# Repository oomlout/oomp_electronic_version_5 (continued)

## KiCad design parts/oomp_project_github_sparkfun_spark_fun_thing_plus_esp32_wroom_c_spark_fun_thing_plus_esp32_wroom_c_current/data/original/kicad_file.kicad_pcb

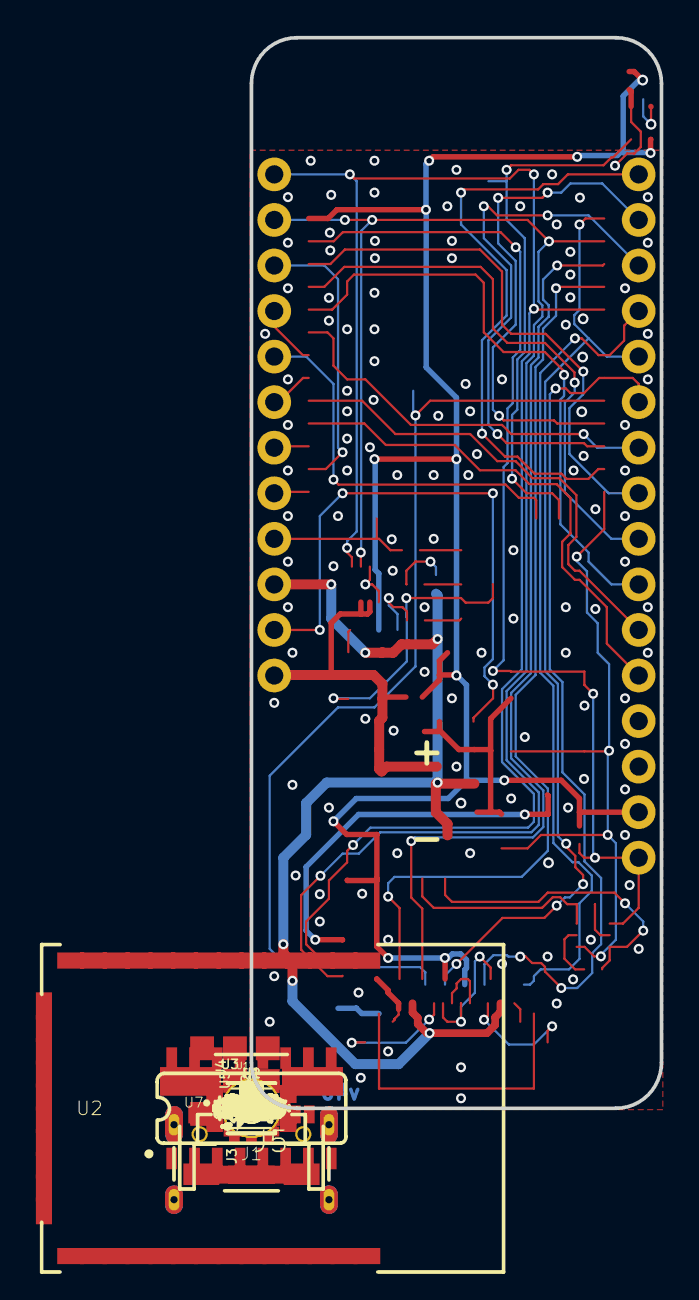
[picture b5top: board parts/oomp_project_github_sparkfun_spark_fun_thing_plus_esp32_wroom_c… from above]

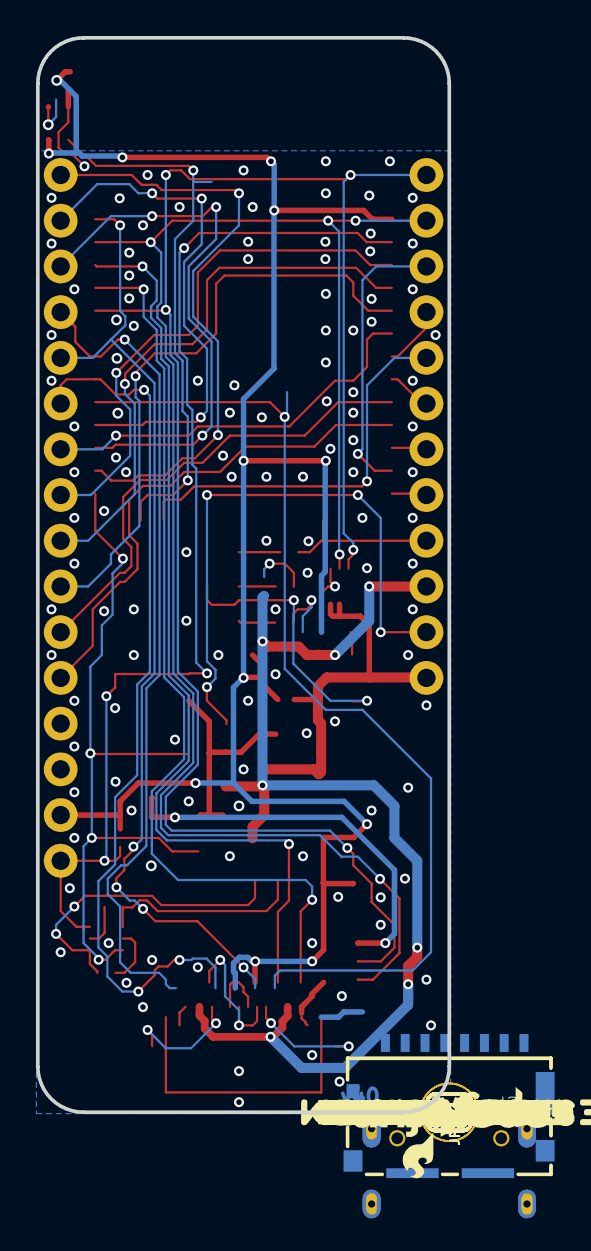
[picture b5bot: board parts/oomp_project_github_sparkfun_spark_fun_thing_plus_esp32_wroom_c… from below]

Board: 2 copper layers, 22.9 x 59.7 mm, 110 parts (46 on the bottom side), 51 nets.

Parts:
C1, C4: 10uF; 0402-TIGHT
C2, C5, C15: 0.1uF; 0402-TIGHT
C3, C7, C10: 1.0uF; 0402-TIGHT
C6: 4.7uF; 0402-TIGHT
C19: 4.7uF; 0603
D1: Yellow; LED-0603
D3: BLUE; LED-0603
D4: 3A/10V/280mV; SOD-323
D5: WS2812; WS2812-2020
D12: RED; LED-0603
FD1, FD2, FD3, FD4: FIDUCIALUFIDUCIAL; FIDUCIAL-MICRO
FRAME1: FRAME-LEDGER; CREATIVE_COMMONS
H1, H2: STAND-OFFTIGHT; STAND-OFF-TIGHT
J1: USB-C-16P-2LAYER-PADS
J2: MICRO-SDFRICTION; MICROSD_TINY
J3: QWIIC_RA; JST04_1MM_RA
J4: JST-2-SMD
J5: THING_PLUS_LOGICAL; THING_PLUS
JP1, JP2, JP3: JUMPER-SMT_2_NC_TRACE_SILK; SMT-JUMPER_2_NC_TRACE_SILK
LOGO1: SFE_LOGO_NAME_FLAME.1_INCH; SFE_LOGO_NAME_FLAME_.1
LOGO2: OSHW-LOGOMINI; OSHW-LOGO-MINI
LOGO4: QWIIC_LOGO_4MM; QWIIC_4MM
Q2: MBT3904DW1T1; SC70-6
Q3: 20V/4.2A/52mΩ/1.4W; SOT23-3
R2, R7, R8, R17, R18: 10k; 0402-TIGHT
R3, R4, R34: 1k; 0402-TIGHT
R6: 2.0k; 0603
R9, R10: 5.1k; 0402-TIGHT
S3: Boot; TACTILE_SWITCH_SMD_4.6X2.8MM
S4: Reset; TACTILE_SWITCH_SMD_4.6X2.8MM
TP1, TP2, TP3, TP4: TEST-POINT3X5; PAD.03X.05
U1: MCP73831; SOT23-5
U2: ESP-WROOM-3232D-NARROW; ESP-WROOM-32D-NARROW
U3, U5: 3.3V; SOT23-5
U4: MAX17048; DFN-8
U7: CH340C; SO016
U$1: SFE_LOGO_FLAME_STOP_.1
U$2: #23#PICO#0
U$3: #19#POCI#0
U$4: #4#FREE#0
U$5: #CHG_LED#0
U$6: ESP32#WROOM0
U$7: THING_PLUS_C0
U$8: #SHLD#0
U$9: #_GND#0
U$10: #_NC#0
U$11: #_3V3#0
U$12: SFE_LOGO_FLAME_.1
U$23: 3V30
U$24: CHG1
U$25: PWR2
U$26: STAT0
U$68: A03
U$69: A12
U$70: A21
U$71: A30
U$72: #17#TX#0
U$73: VB1
U$74: EN3
U$75: GND1
U$76: VU0
U$77: 130
U$78: BOOT0
U$79, U$109: #RST#0
U$80: RST0
U$81: #16#RX#0
U$83: #18#SCK#0
U$84: #35#A5#0
U$85: #36#A4#0
U$86: #25#A1#2
U$87: #26#A0#3
U$88: #34#A2#1
U$89: #39#A3#0
U$90: #12#4
U$91: #14#9
U$92: #15#7
U$93: #27#5
U$94: #32#8
U$95: #33#6
U$96: #EN#1
U$97: #VBAT#0
U$98: #VUSB#2
U$99: #13#LED#0
U$100: #21#SDA#1
U$101: #22#SCL#0
U$102: #PWR#0
U$107: NC0

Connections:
3.3V: C1.1, C2.1, C4.1, C5.1, C10.1, D5.VCC, J2.4, J5.27, JP1.2, R2.2, U2.2, U3.5, U7.4, U7.16
CH340-DTR: Q2.1, R17.1, U7.13
CH340-RTS: Q2.4, R18.1, U7.14
CH340-RX: U2.35, U7.3
CH340-TX: U2.34, U7.2
CHG_LED: D1.A, R3.2
D+: J1.A6, J1.B6, U7.5
D-: J1.A7, J1.B7, U7.6
DTR-10K: Q2.5, R17.2
ESP_0/QPWR: Q2.6, S3.3, S3.4, TP1.1, U2.25, U5.3
ESP_2/RGB_DI: D5.DI, TP3.1, U2.24
ESP_4/TP_FB: J5.13, U2.26
ESP_5/SD_CS: J2.2, TP4.1, U2.29
ESP_12/GPIO1: J5.8, U2.14
ESP_13/GPIO0/LED: J5.9, R4.1, U2.16
ESP_14/GPIO6: J5.3, U2.13
ESP_15/GPIO4: J5.5, U2.23
ESP_16/TP_RX: J5.15, U2.27
ESP_17/TP_TX: J5.14, U2.28
ESP_18/TP_SCK: J2.5, J5.18, U2.30
ESP_19/TP_POCI: J2.7, J5.16, U2.31
ESP_21/TP_SDA: J3.3, J5.1, U2.33, U4.8
ESP_22/TP_SCL: J3.4, J5.2, U2.36, U4.7
ESP_23/TP_PICO: J2.3, J5.17, U2.37
ESP_25/TP_A1: J5.23, U2.10
ESP_26/TP_A0: J5.24, U2.11
ESP_27/GPIO2: J5.7, U2.12
ESP_32/GPIO5: J5.4, U2.8
ESP_33/GPIO3: J5.6, U2.9
ESP_34/TP_A2: J5.22, U2.6
ESP_35/TP_A5: J5.19, U2.7
ESP_36/TP_A4: J5.20, U2.4
ESP_39/TP_A3: J5.21, U2.5
GND: C1.2, C2.2, C3.2, C4.2, C5.2, C6.2, C7.2, C10.2, C15.2, C19.2, D3.C, D5.GND, D12.C, J1.GND, J1.GND2, J2.6, J2.GND1, J2.GND2, J2.GND3, J2.GND4, J2.GND5, J2.GND6, J3.1, J4.1, J5.25, JP3.1, R6.1, R7.1, R9.1, R10.1, S3.1, S3.2, S4.1, S4.2, U1.2, U2.1, U2.15, U2.38, U2.GND1, U2.GNDT1, U2.GNDT2, U2.GNDT3, U2.GNDT4, U2.GNDT5, U2.GNDT6, U2.GNDT7, U2.GNDT8, U3.2, U4.1, U4.4, U4.6, U4.9, U5.2, U7.1
unnamed: JP1.1, R34.1
unnamed: D3.A, R4.2
unnamed: D5.DO, TP2.1
unnamed: JP2.1, R3.1
unnamed: J1.B5, R9.2
unnamed: J1.A5, R10.2
unnamed: D1.C, U1.1
unnamed: J1.SHLD1, J1.SHLD2, J1.SHLD3, J1.SHLD4, JP3.2
unnamed: R6.2, U1.5
unnamed: D12.A, R34.2
QWIIC_PWR: C3.1, J3.2, U5.5
RTS-10K: Q2.2, R18.2
TP_EN: J5.11, R8.2, U3.3
VIN: C7.1, D4.C, Q3.2, R8.1, U3.1, U5.1
V_BATT: C6.1, C15.1, J4.2, J5.12, Q3.3, U1.3, U4.2, U4.3
V_USB: C19.1, D4.A, J1.VBUS1, J1.VBUS2, J5.10, JP2.2, Q3.1, R7.2, U1.4
~RESET: J5.28, Q2.3, R2.1, S4.3, S4.4, U2.3

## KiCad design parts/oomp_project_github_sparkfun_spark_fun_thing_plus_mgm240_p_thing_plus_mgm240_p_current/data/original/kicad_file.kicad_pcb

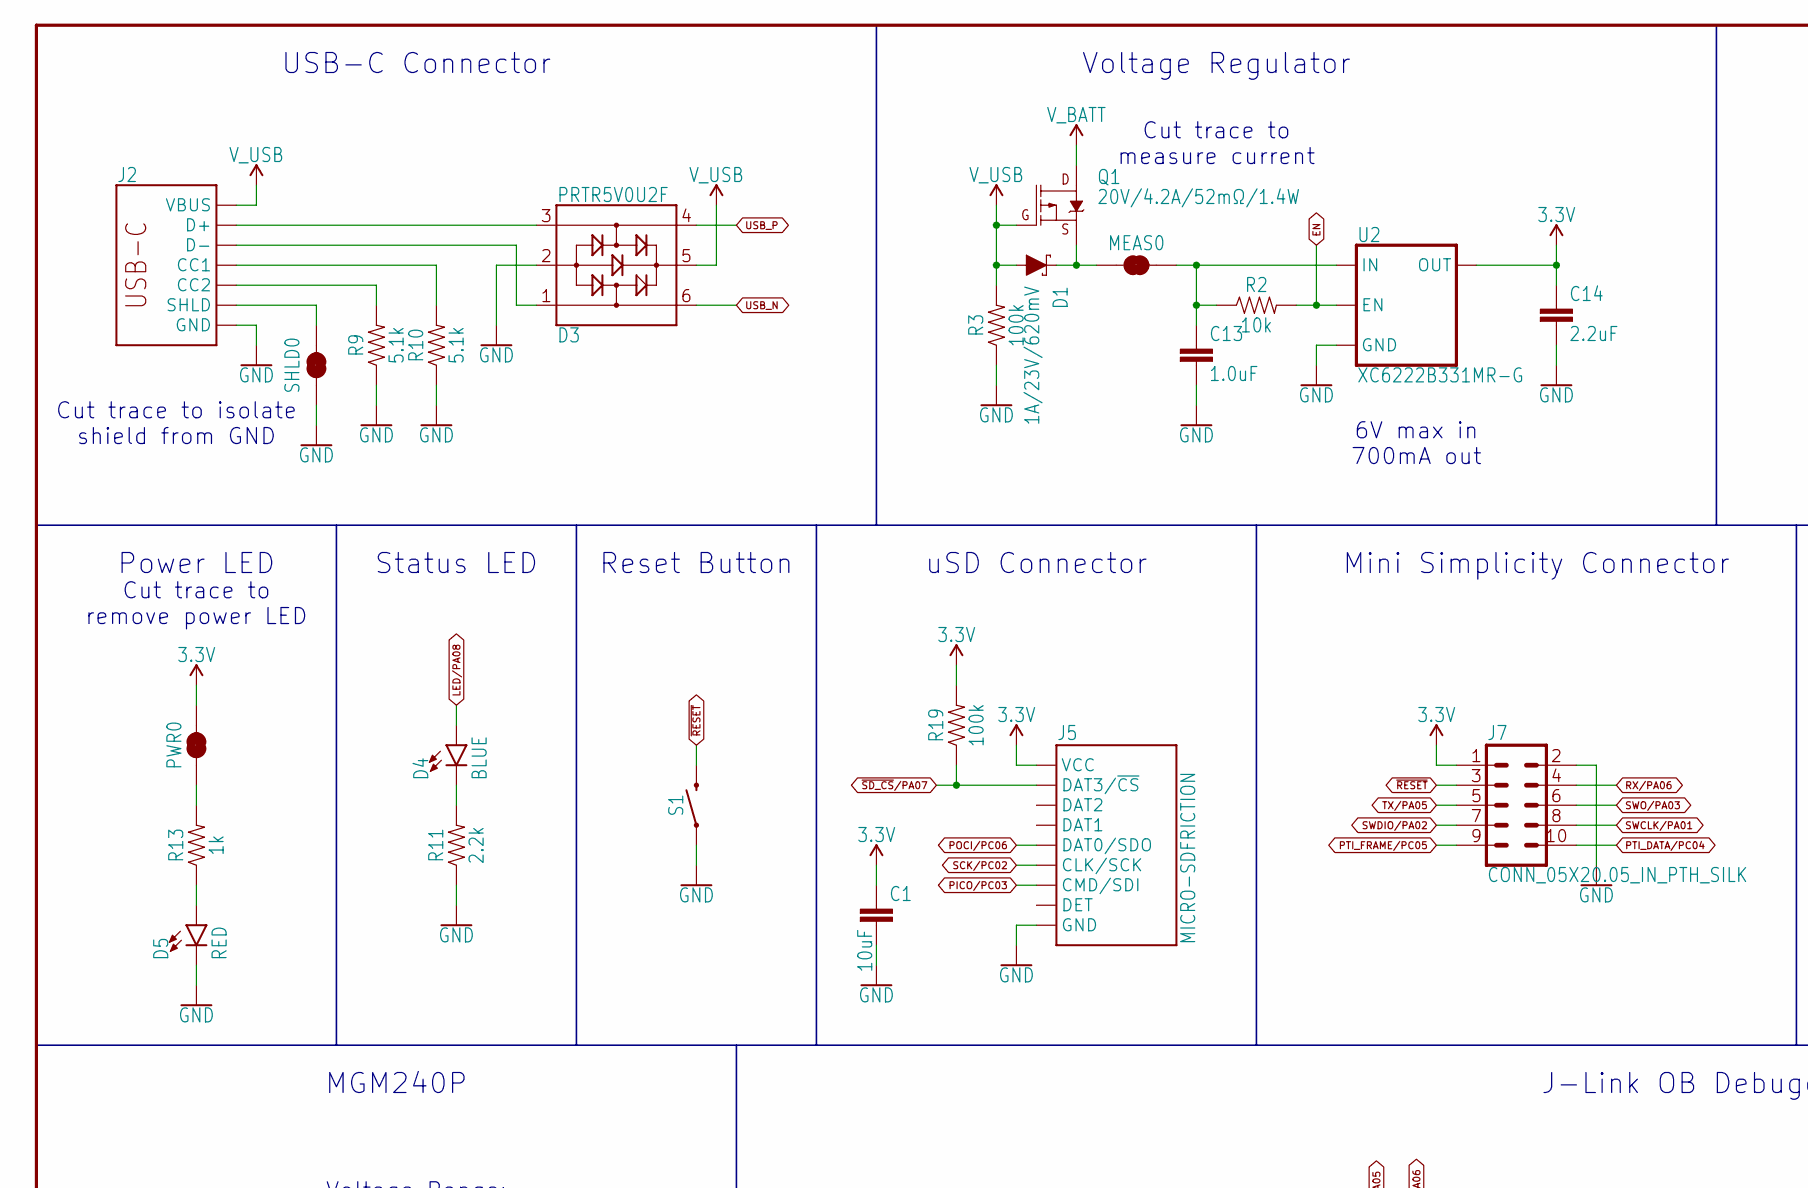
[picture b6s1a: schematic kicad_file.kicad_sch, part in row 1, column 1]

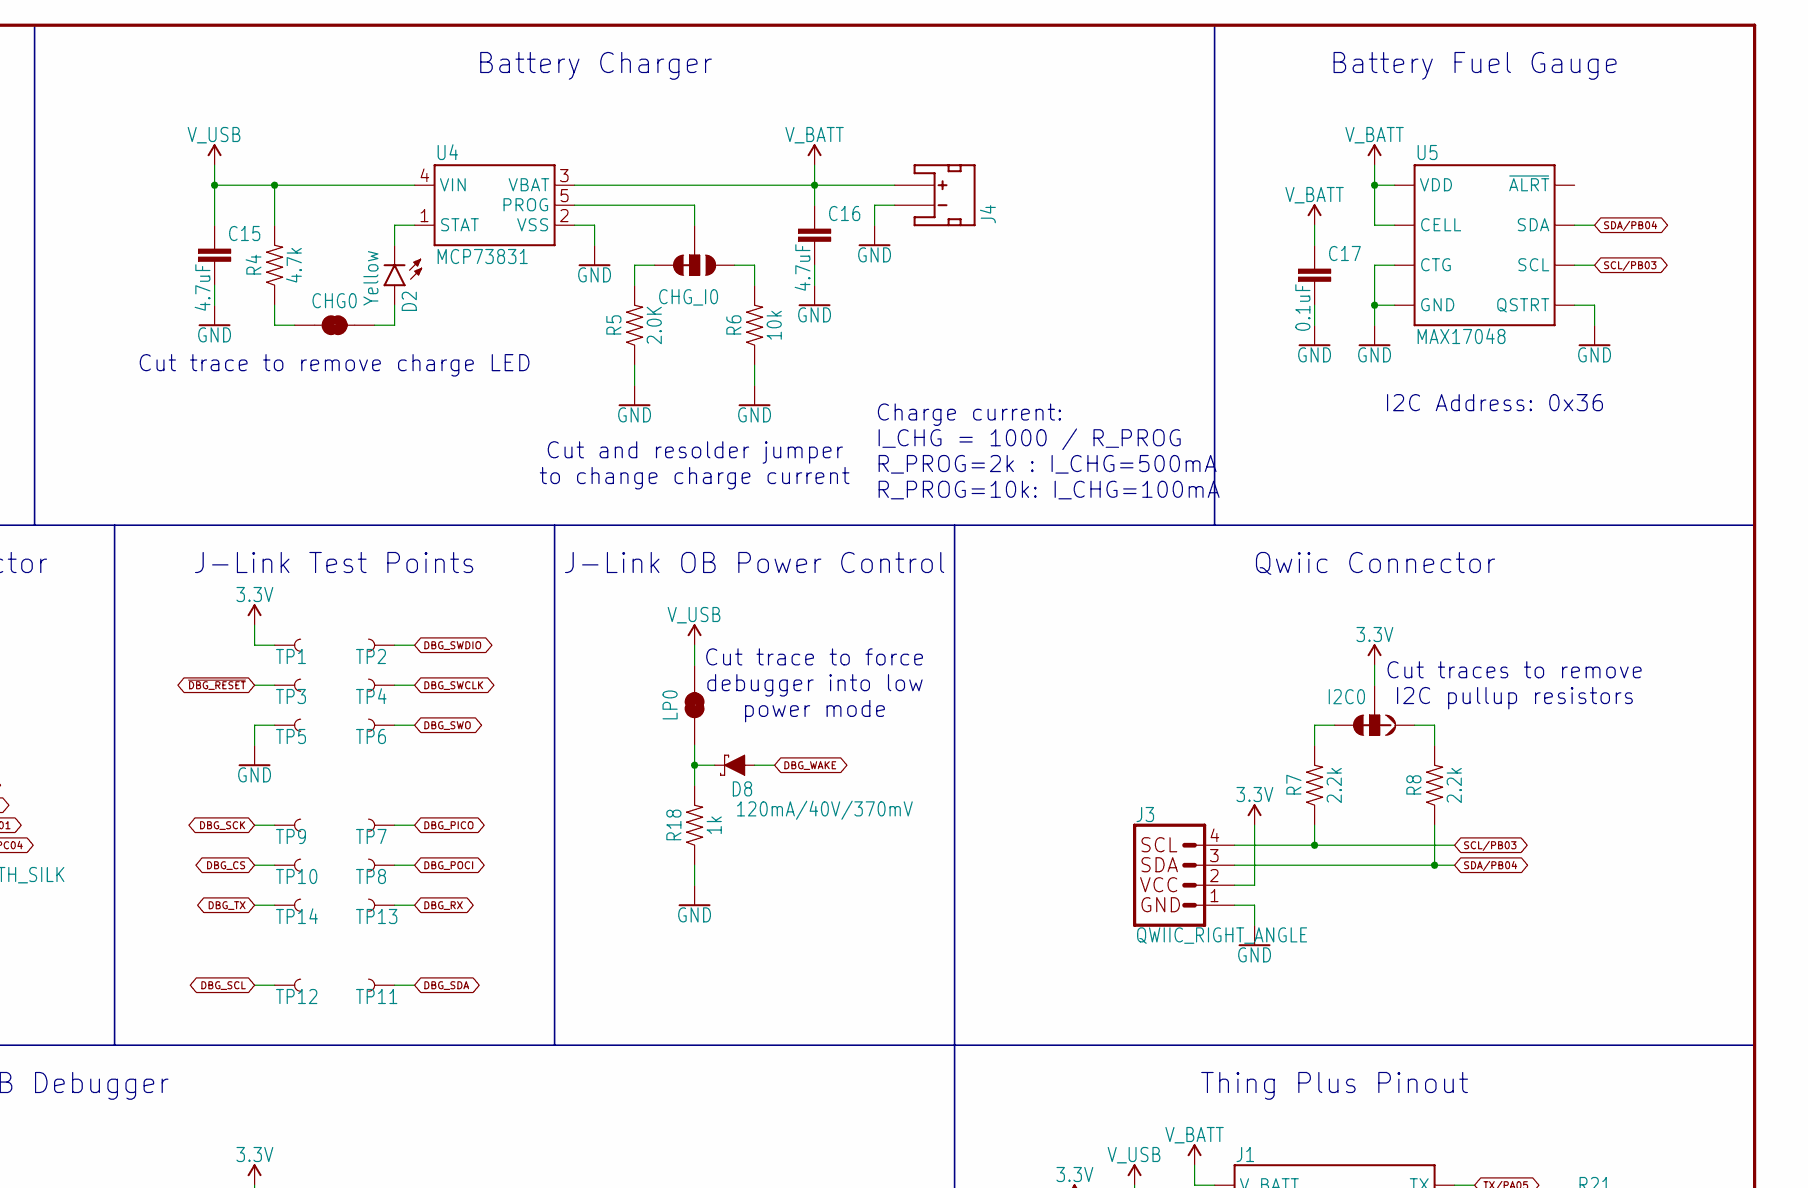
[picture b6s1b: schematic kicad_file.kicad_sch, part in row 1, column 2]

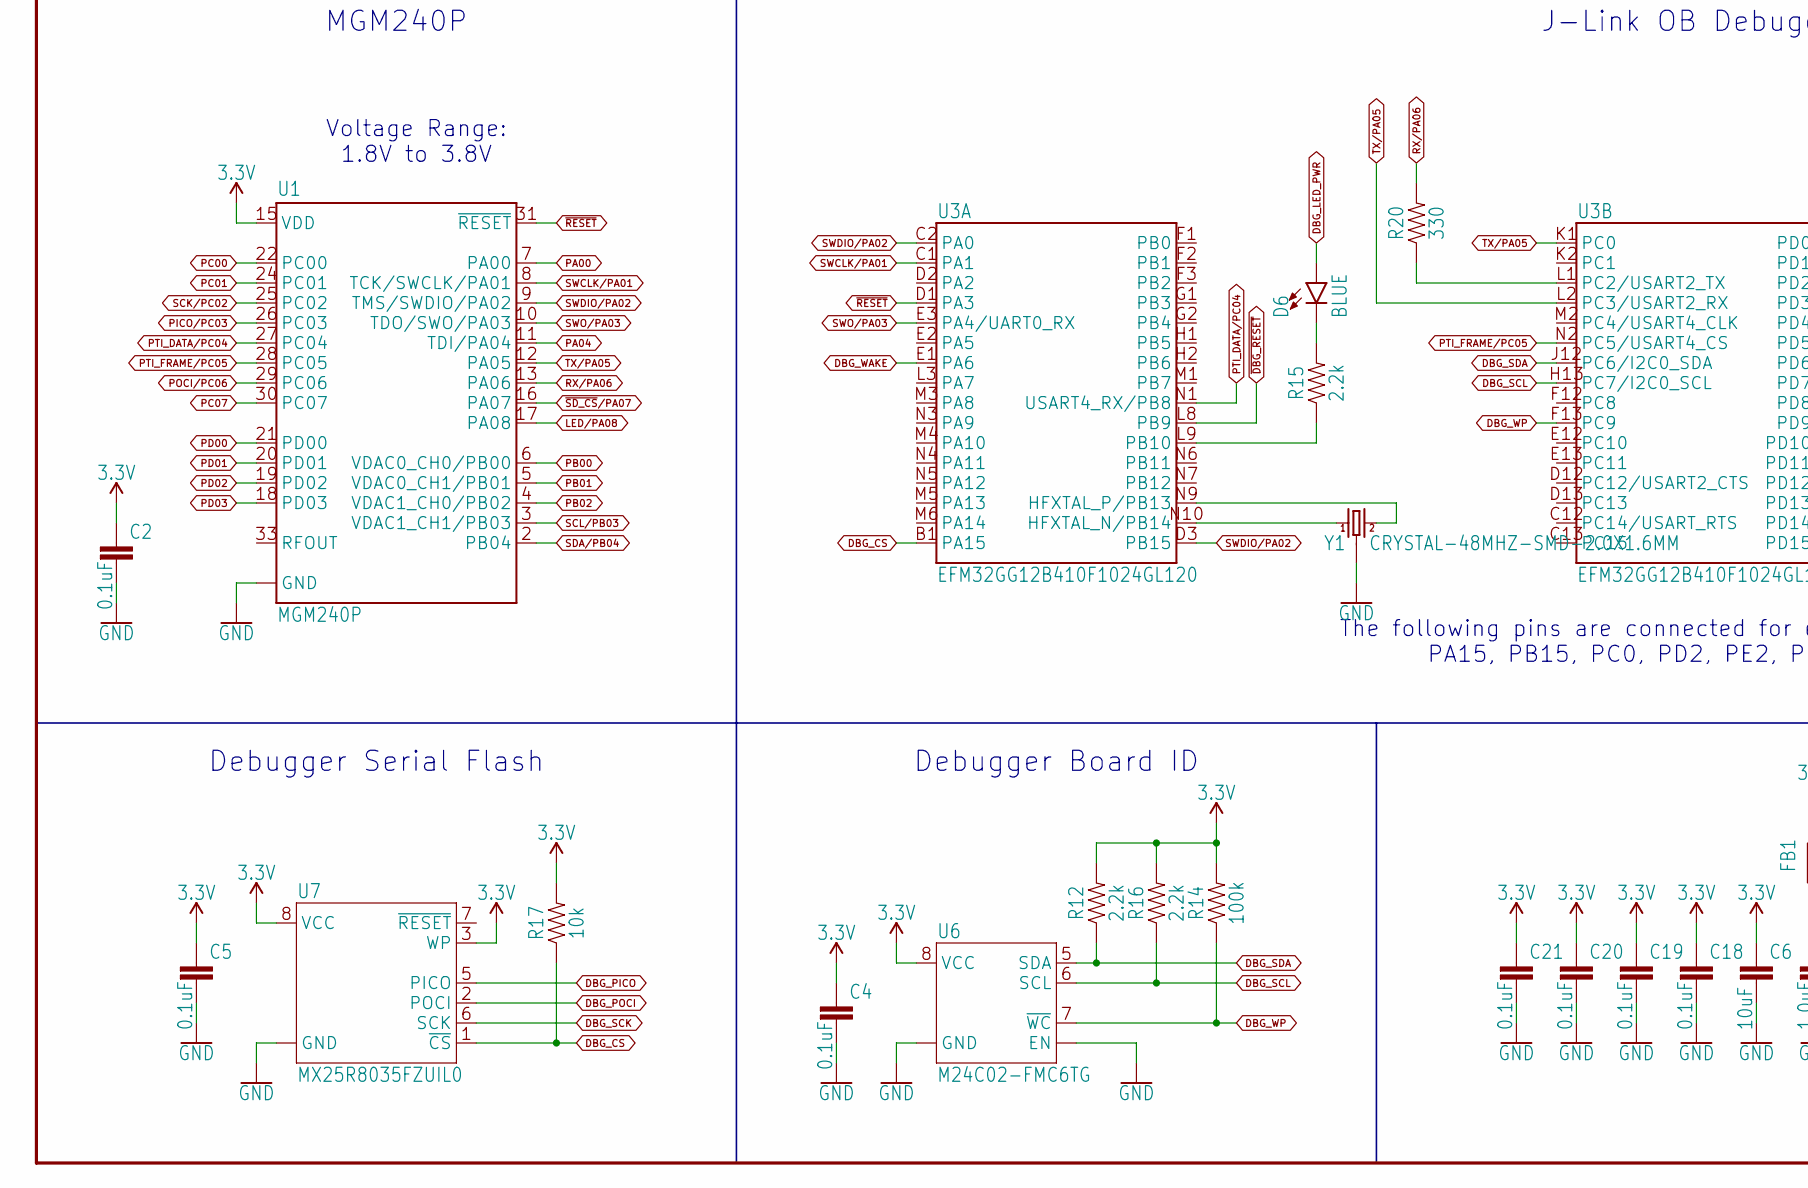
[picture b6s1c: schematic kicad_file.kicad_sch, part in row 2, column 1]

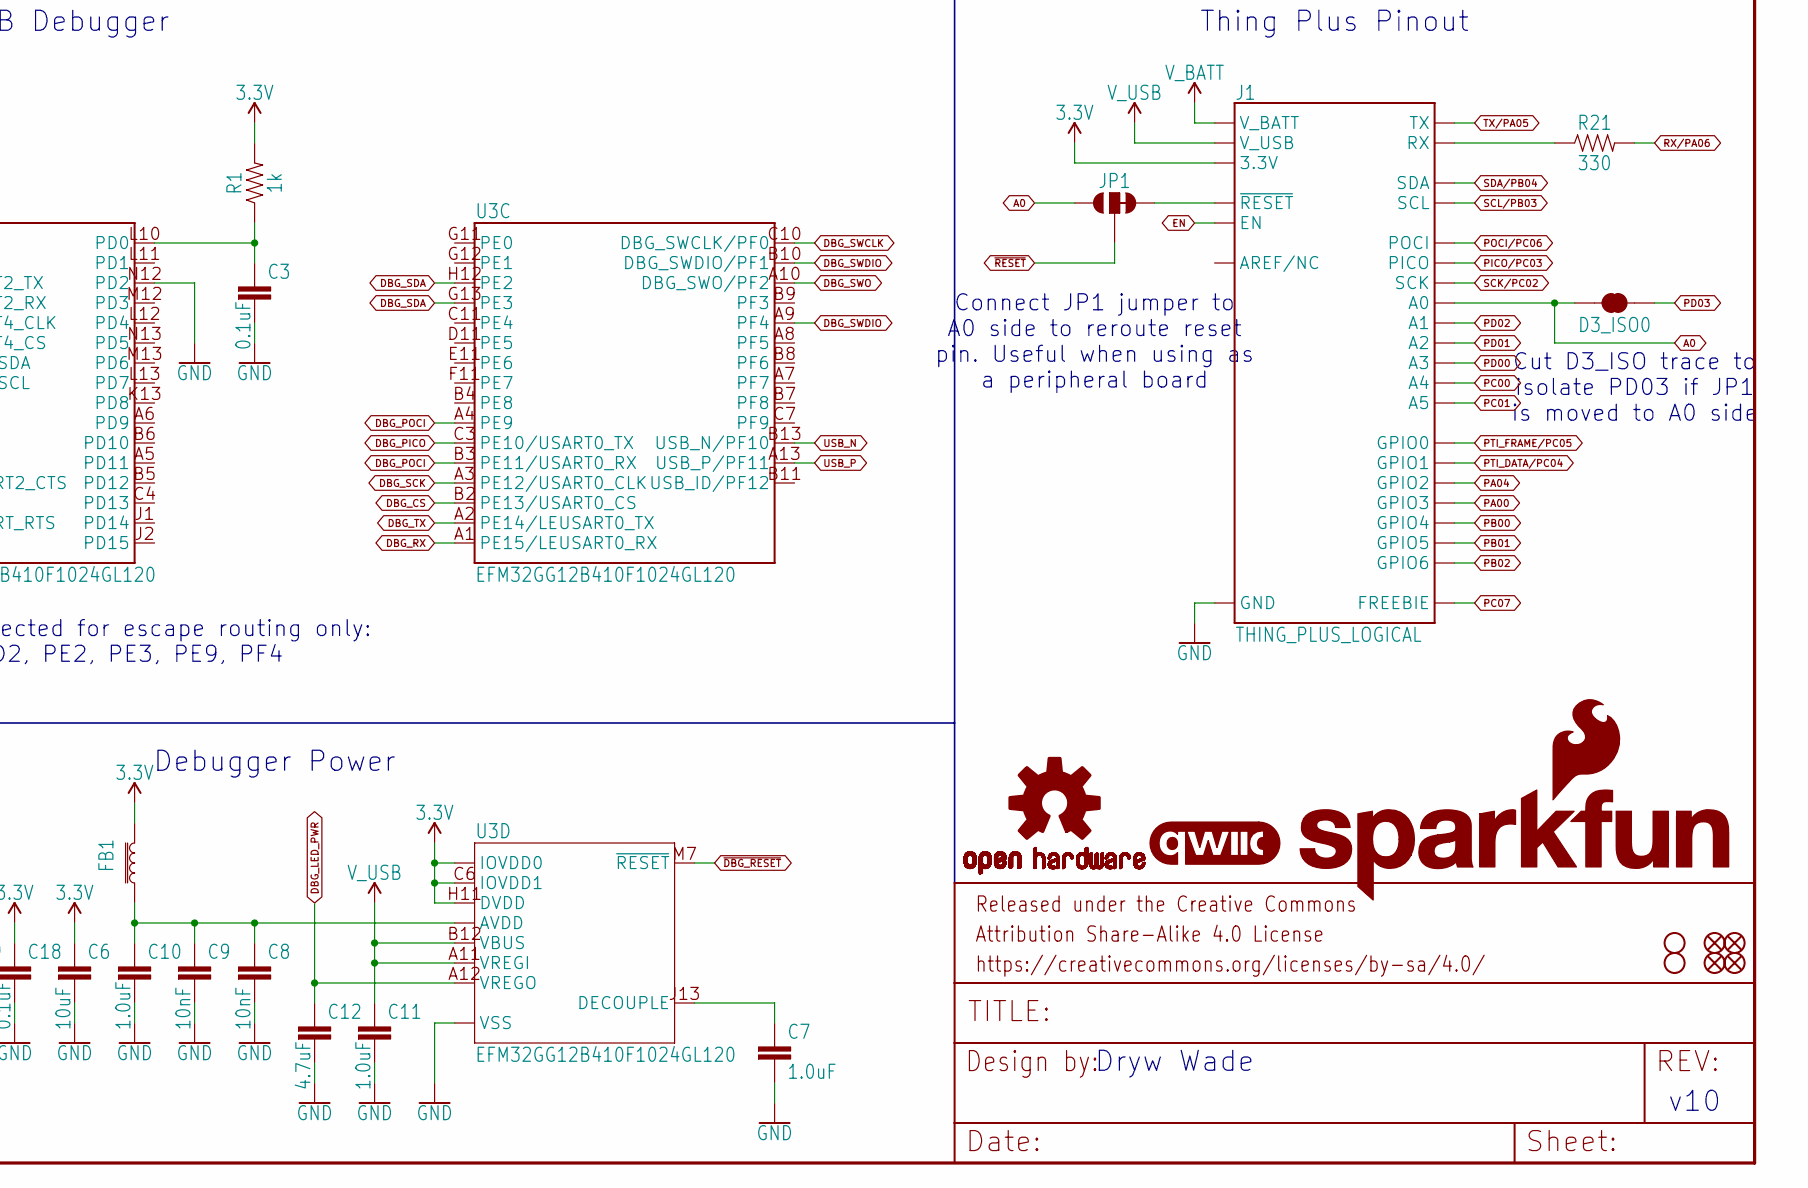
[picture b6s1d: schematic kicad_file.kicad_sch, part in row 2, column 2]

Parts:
C1, C6: 10uF; 0402-TIGHT
C2, C3, C4, C5, C17, C18, C19, C20, C21: 0.1uF; 0402-TIGHT
C7: 1.0uF; 0603
C8, C9: 10nF; 0402-TIGHT
C10, C11, C13: 1.0uF; 0402-TIGHT
C12, C15, C16: 4.7uF; 0402-TIGHT
C14: 2.2uF; 0402-TIGHT
CHG0: JUMPER-SMT_2_NC_TRACE_SILK; SMT-JUMPER_2_NC_TRACE_SILK
CHG_I0: JUMPER-SMT_3_1-NC_TRACE_SILK; SMT-JUMPER_3_1-NC_TRACE_SILK
D1: 1A/23V/620mV; SOD-323
D2: Yellow; LED-0603
D3: PRTR5V0U2F; SOT886
D3_ISO0: JUMPER-SMT_2_NC_TRACE_SILK; SMT-JUMPER_2_NC_TRACE_SILK
D4, D6: BLUE; LED-0603
D5: RED; LED-0603
D8: 120mA/40V/370mV; SOD-523
FB1: FERRITE_BEAD-120_OHM-0402T; 0402-TIGHT
FD1, FD2, FD3, FD4: FIDUCIAL1X2; FIDUCIAL-1X2
FRAME1: FRAME-LEDGER; CREATIVE_COMMONS
H1, H2: STAND-OFF
I2C0: JUMPER-SMT_3_2-NC_TRACE_SILK; SMT-JUMPER_3_2-NC_TRACE_SILK
J1: THING_PLUS_LOGICAL; THING_PLUS
J2: USB Female Type C Connector; USB-C-16P-4LAYER-ISOLATED
J3: QWIIC_RIGHT_ANGLE; JST04_1MM_RA
J4: JST_2MM_MALE; JST-2-SMD
J5: MICRO-SDFRICTION; MICROSD_TINY
J7: CONN_05X20.05_IN_PTH_SILK; 2X5_PTH_SILK_.05
JP1: JUMPER-SMT_3_1-NC_TRACE_SILK; SMT-JUMPER_3_1-NC_TRACE_SILK
LOGO1: SFE_LOGO_NAME_FLAME.1_INCH; SFE_LOGO_NAME_FLAME_.1
LOGO2: QWIIC_LOGO_3MM; QWIIC_3MM
LOGO3: OSHW-LOGOS; OSHW-LOGO-S
LP0: JUMPER-SMT_2_NC_TRACE_SILK; SMT-JUMPER_2_NC_TRACE_SILK
MEAS0: JUMPER-COMBO_2_NC_TRACE; COMBO-JUMPER_2_NC_TRACE
PWR0: JUMPER-SMT_2_NC_TRACE_SILK; SMT-JUMPER_2_NC_TRACE_SILK
Q1: 20V/4.2A/52mΩ/1.4W; SOT23-3
R1, R13, R18: 1k; 0402-TIGHT
R2, R6, R17: 10k; 0402-TIGHT
R3, R14, R19: 100k; 0402-TIGHT
R4: 4.7k; 0402-TIGHT
R5: 2.0K; 0402-TIGHT
R7, R8, R11, R12, R15, R16: 2.2k; 0402-TIGHT
R9, R10: 5.1k; 0402-TIGHT
R20, R21: 330; 0402-TIGHT
S1: MOMENTARY-SWITCH-SPST-SMD-4.6X2.8MM; TACTILE_SWITCH_SMD_4.6X2.8MM
SHLD0: JUMPER-SMT_2_NC_TRACE_SILK; SMT-JUMPER_2_NC_TRACE_SILK
TP1, TP2, TP3, TP4, TP5, TP6, TP7, TP8, TP9, TP10, TP11, TP12, TP13, TP14: TEST-POINT3; PAD.03X.03
U1: MGM240P
U2: XC6222B331MR-G; SOT23-5
U3: EFM32GG12B410F1024GL120; BGA120
U4: MCP73831; SOT23-5
U5: MAX17048; DFN-8
U6: M24C02-FMC6TG; DFN8_2X3MM
U7: MX25R8035FZUIL0; USON-8_2X3MM
Y1: CRYSTAL-48MHZ-SMD-2.0X1.6MM; CRYSTAL-SMD-2.0X1.6MM-ECS

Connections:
3.3V: C1.1, C2.1, C4.1, C5.1, C6.1, C14.1, C18.1, C19.1, C20.1, C21.1, FB1.2, I2C0.2, J1.27 (3.3V), J3.2, J5.4 (VCC), J7.1, PWR0.2, R1.2, R12.2, R14.2, R16.2, R17.2, R19.2, TP1.1, U1.15 (VDD), U2.5 (OUT), U3.C6 (IOVDD1), U3.C9 (IOVDD0), U3.G3 (IOVDD0), U3.H11 (DVDD), U3.J11 (IOVDD0), U3.K3 (IOVDD0), U3.L4 (IOVDD0), U3.L7 (IOVDD0), U6.8 (VCC), U7.3 (WP), U7.8 (VCC)
A0: D3_ISO0.2, J1.24 (A0), JP1.1
DBG_CS: R17.1, TP10.1, U3.B1 (PA15), U3.B2 (PE13/USART0_CS), U7.1 (~CS)
DBG_LED_PWR: C12.1, D6.A, U3.A12 (VREGO)
DBG_PICO: TP7.1, U3.C3 (PE10/USART0_TX), U7.5 (PICO)
DBG_POCI: TP8.1, U3.A4 (PE9), U3.B3 (PE11/USART0_RX), U7.2 (POCI)
DBG_RX: TP13.1, U3.A1 (PE15/LEUSART0_RX)
DBG_SCK: TP9.1, U3.A3 (PE12/USART0_CLK), U7.6 (SCK)
DBG_SCL: R16.1, TP12.1, U3.H13 (PC7/I2C0_SCL), U6.6 (SCL)
DBG_SDA: R12.1, TP11.1, U3.G13 (PE3), U3.H12 (PE2), U3.J12 (PC6/I2C0_SDA), U6.5 (SDA)
DBG_SWCLK: TP4.1, U3.C10 (DBG_SWCLK/PF0)
DBG_SWDIO: TP2.1, U3.A9 (PF4), U3.B10 (DBG_SWDIO/PF1)
DBG_SWO: TP6.1, U3.A10 (DBG_SWO/PF2)
DBG_TX: TP14.1, U3.A2 (PE14/LEUSART0_TX)
DBG_WAKE: D8.A, U3.E1 (PA6)
DBG_WP: R14.1, U3.F13 (PC9), U6.7 (~WC)
EN: J1.11 (EN), R2.2, U2.3 (EN)
GND: C1.2, C2.2, C3.2, C4.2, C5.2, C6.2, C7.2, C8.2, C9.2, C10.2, C11.2, C12.2, C13.2, C14.2, C15.2, C16.2, C17.2, C18.2, C19.2, C20.2, C21.2, D3.2, D5.C, J1.25 (GND), J2.GND, J2.GND2 (GND), J3.1, J4.1 (-), J5.6 (GND), J5.GND1 (GND), J5.GND2 (GND), J5.GND3 (GND), J5.GND4 (GND), J5.GND5 (GND), J5.GND6 (GND), J7.2, R3.1, R5.1, R6.1, R9.1, R10.1, R11.1, R18.1, S1.1, S1.2 (1), SHLD0.1, TP5.1, U1.1 (GND), U1.14 (GND), U1.23 (GND), U1.32 (GND), U1.34 (GND), U1.35 (GND), U1.36 (GND), U2.2 (GND), U3.C5 (VSS), U3.C8 (VSS), U3.H3 (VSS), U3.J3 (VSS), U3.K11 (VSS), U3.K12 (VSS), U3.L5 (VSS), U3.L6 (VSS), U3.M8 (VSS), U3.M11 (VSS), U3.N8 (VSS), U3.N12 (PD2), U4.2 (VSS), U5.1 (CTG), U5.4 (GND), U5.6 (QSTRT), U5.9 (GND), U6.1 (EN), U6.2 (EN), U6.3 (EN), U6.4 (GND), U6.EPAD (GND), U7.4 (GND), U7.EPAD (GND), Y1.2 (GND), Y1.4 (GND)
LED/PA08: D4.A, U1.17 (PA08)
unnamed: D4.C, R11.2
unnamed: PWR0.1, R13.2
unnamed: CHG0.2, D2.A
unnamed: CHG_I0.1, R6.2
unnamed: D2.C, U4.1 (STAT)
unnamed: CHG_I0.3, R5.2
unnamed: D1.C, MEAS0.1, MEAS0.3 (1), Q1.2 (S)
unnamed: D5.A, R13.1
unnamed: CHG_I0.2, U4.5 (PROG)
unnamed: CHG0.1, R4.1
unnamed: I2C0.3, R7.2
unnamed: C3.1, R1.1, U3.L10 (PD0)
unnamed: I2C0.1, R8.2
unnamed: J2.B5 (CC2), R9.2
unnamed: J2.A5 (CC1), R10.2
unnamed: D3.3, J2.A6 (D+), J2.B6 (D+)
unnamed: C7.1, U3.J13 (DECOUPLE)
unnamed: D3.1, J2.A7 (D-), J2.B7 (D-)
unnamed: C8.1, C9.1, C10.1, FB1.1, U3.M9 (AVDD), U3.M10 (AVDD), U3.N11 (AVDD)
unnamed: R15.1, U3.L9 (PB10)
unnamed: D6.C, R15.2
unnamed: U3.N10 (HFXTAL_N/PB14), Y1.1
unnamed: U3.N9 (HFXTAL_P/PB13), Y1.3 (2)
unnamed: D8.C, LP0.1, R18.2
unnamed: R20.1, U3.L1 (PC2/USART2_TX)
unnamed: J1.15 (RX), R21.1
unnamed: C13.1, MEAS0.2, MEAS0.4 (2), R2.1, U2.1 (IN)
unnamed: J1.28 (~RESET), JP1.3
PA00: J1.6 (GPIO3), U1.7 (PA00)
PA04: J1.7 (GPIO2), U1.11 (TDI/PA04)
PB00: J1.5 (GPIO4), U1.6 (VDAC0_CH0/PB00)
PB01: J1.4 (GPIO5), U1.5 (VDAC0_CH1/PB01)
PB02: J1.3 (GPIO6), U1.4 (VDAC1_CH0/PB02)
PC00: J1.20 (A4), U1.22 (PC00)
PC01: J1.19 (A5), U1.24 (PC01)
PC07: J1.13 (FREEBIE), U1.30 (PC07)
PD00: J1.21 (A3), U1.21 (PD00)
PD01: J1.22 (A2), U1.20 (PD01)
PD02: J1.23 (A1), U1.19 (PD02)
PD03: D3_ISO0.1, U1.18 (PD03)
PICO/PC03: J1.17 (PICO), J5.3 (CMD/SDI), U1.26 (PC03)
POCI/PC06: J1.16 (POCI), J5.7 (DAT0/SDO), U1.29 (PC06)
PTI_DATA/PC04: J1.8 (GPIO1), J7.10, U1.27 (PC04), U3.N1 (USART4_RX/PB8)
PTI_FRAME/PC05: J1.9 (GPIO0), J7.9, U1.28 (PC05), U3.N2 (PC5/USART4_CS)
RX/PA06: J7.4, R20.2, R21.2, U1.13 (PA06)
SCK/PC02: J1.18 (SCK), J5.5 (CLK/SCK), U1.25 (PC02)
SCL/PB03: J1.2 (SCL), J3.4, R7.1, U1.3 (VDAC1_CH1/PB03), U5.7 (SCL)
SDA/PB04: J1.1 (SDA), J3.3, R8.1, U1.2 (PB04), U5.8 (SDA)
SHLD: J2.SHLD1 (SHLD), J2.SHLD2 (SHLD), J2.SHLD3 (SHLD), J2.SHLD4 (SHLD), J2.SHLD5 (SHLD), J2.SHLD6 (SHLD), J2.SHLD7 (SHLD), J2.SHLD8 (SHLD), SHLD0.2
SWCLK/PA01: J7.8, U1.8 (TCK/SWCLK/PA01), U3.C1 (PA1)
SWDIO/PA02: J7.7, U1.9 (TMS/SWDIO/PA02), U3.C2 (PA0), U3.D3 (PB15)
SWO/PA03: J7.6, U1.10 (TDO/SWO/PA03), U3.E3 (PA4/UART0_RX)
TX/PA05: J1.14 (TX), J7.5, U1.12 (PA05), U3.K1 (PC0), U3.L2 (PC3/USART2_RX)
USB_N: D3.6, U3.B13 (USB_N/PF10)
USB_P: D3.4, U3.A13 (USB_P/PF11)
V_BATT: C16.1, C17.1, J1.12 (V_BATT), J4.2 (+), Q1.3 (D), U4.3 (VBAT), U5.2 (CELL), U5.3 (VDD)
V_USB: C11.1, C15.1, D1.A, D3.5, J1.10 (V_USB), J2.VBUS1 (VBUS), J2.VBUS2 (VBUS), LP0.2, Q1.1 (G), R3.2, R4.2, U3.A11 (VREGI), U3.B12 (VBUS), U4.4 (VIN)
~DBG_RESET: TP3.1, U3.L8 (PB9), U3.M7 (~RESET)
~RESET: J7.3, JP1.2, S1.3 (2), S1.4 (2), U1.31 (~RESET), U3.D1 (PA3)
~SD_CS/PA07: J5.2 (DAT3/~CS), R19.1, U1.16 (PA07)

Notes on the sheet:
Mini Simplicity Connector
Battery Fuel Gauge
I2C Address: 0x36
uSD Connector
Cut trace to remove power LED
Thing Plus Pinout
Cut trace to isolate shield from GND
Power LED
6V max in 700mA out
Cut trace to remove charge LED
J-Link OB Debugger
Status LED
Dryw Wade
Cut traces to remove I2C pullup resistors
Connect JP1 jumper to A0 side to reroute reset pin. Useful when using as a peripheral board
v10
USB-C Connector
Debugger Power
Cut D3_ISO trace to isolate PD03 if JP1 is moved to A0 side
Qwiic Connector
Cut trace to force debugger into low power mode
Charge current: I_CHG = 1000 / R_PROG R_PROG=2k : I_CHG=500mA R_PROG=10k: I_CHG=100mA
Voltage Range: 1.8V to 3.8V
The following pins are connected for escape routing only: PA15, PB15, PC0, PD2, PE2, PE3, PE9, PF4
J-Link Test Points
Battery Charger
Debugger Board ID
Cut trace to measure current
MGM240P
J-Link OB Power Control
Voltage Regulator
Reset Button
Debugger Serial Flash
Cut and resolder jumper to change charge current

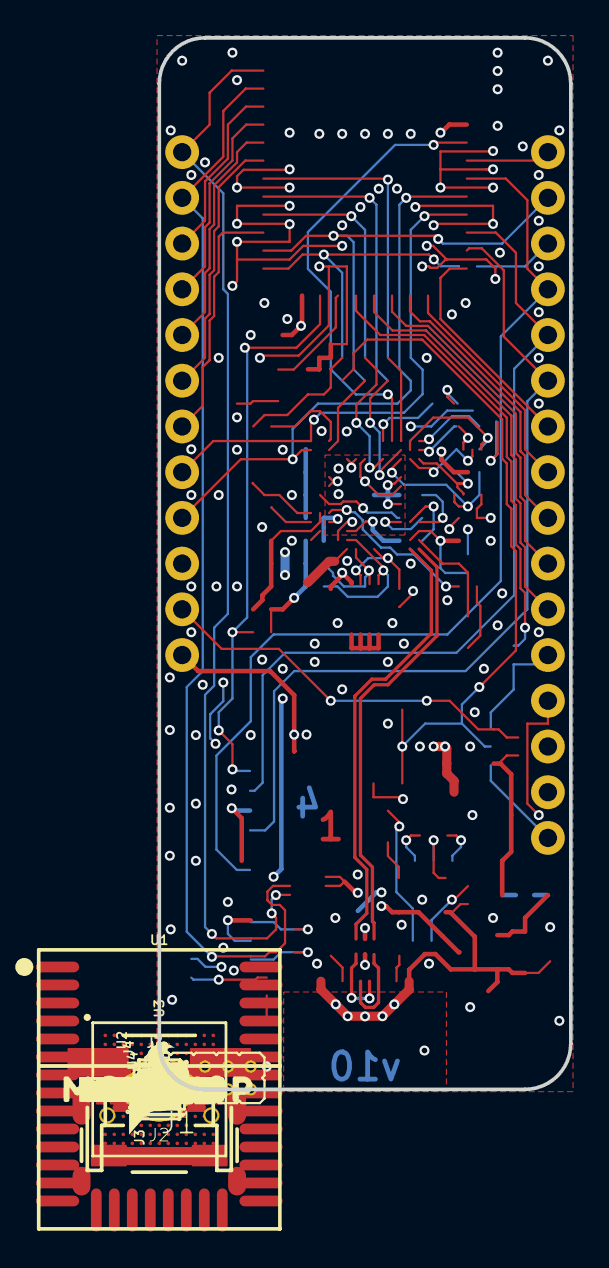
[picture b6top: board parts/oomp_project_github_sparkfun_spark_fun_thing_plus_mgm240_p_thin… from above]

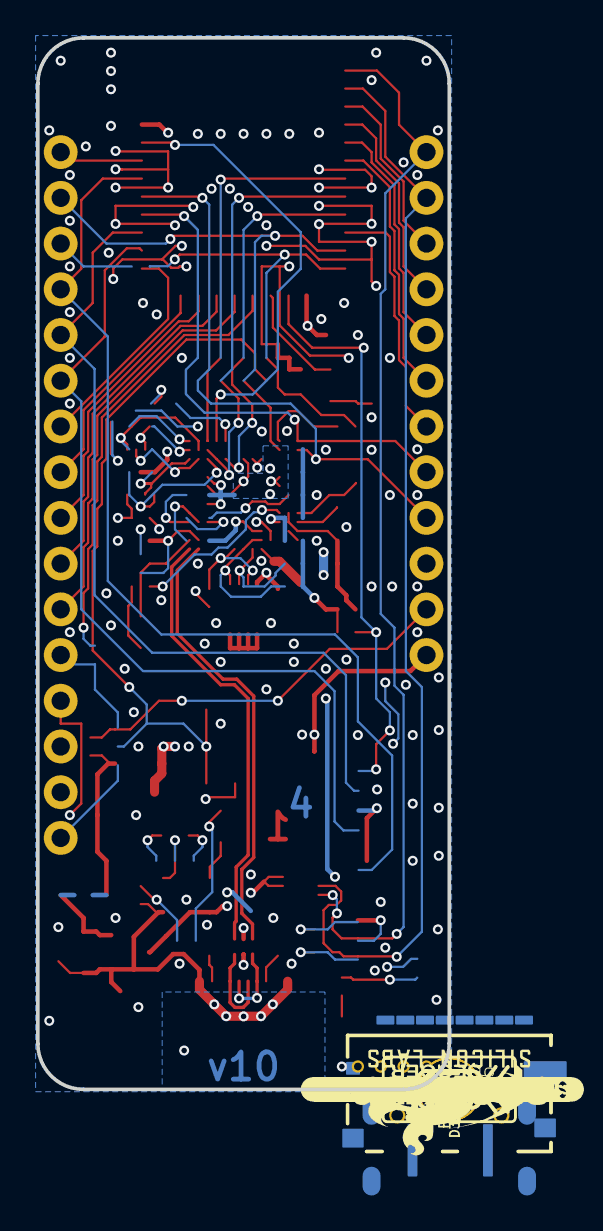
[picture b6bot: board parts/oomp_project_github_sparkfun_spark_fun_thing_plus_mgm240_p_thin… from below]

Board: 4 copper layers, 22.9 x 58.4 mm, 182 parts (80 on the bottom side), 79 nets.

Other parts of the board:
U$1: #_B4#0
U$2: #_B3#0
U$3: #_B2#0
U$4: #_B1#0
U$5: #SHLD#0
U$6: #_B0#0
U$7: #_A0#0
U$8: #_A4#0
U$9: #_C5#0
U$10: #_C4#0
U$11: #C7_#0
U$12: #A5_#0
U$13: #A6_#0
U$14: #C6_#0
U$15: #C3_#0
U$16: #C2_#0
U$17: #C1_#0
U$18: #C0_#0
U$19: #PWR#0
U$20: PWR0
U$21: #GND_#0
U$22: #3V3_#0
U$23, U$58: MGM240P0
U$24: #D0_#0
U$25: #_VB#0
U$26: #_VU#0
U$27: #_EN#0
U$28: ##RST##0
U$29: SFE_LOGO_FLAME_.2
U$30: #0
U$31: #1
U$32: #D1_#0
U$33: #LP#0
U$34: #_A6#RX#0
U$35: #_C6#POCI#0
U$36: #_C3#PICO#0
U$37: #_C2#SCK#0
U$38: MINI_SIMPLICITY0
U$39: #_C1#0
U$40: #_C0#0
U$41: #_D0#0
U$42: #_D1#0
U$43: #_GND#0
U$44: #_3V3#0
U$45: #_#RST##0
U$46: #_D2#0
U$47: SEGGER_LOGO_7.5MM
U$48: #C4_#0
U$49: #C5_#0
U$50: #A4_#0
U$51: #A0_#0
U$52: #B0_#0
U$53: #B2_#0
U$54: #B1_#0
U$55: #VBAT_#0
U$56: #VUSB_#0
U$57: #EN_#0
U$59: #MEAS#0
U$60: #CHG#0
U$61: #I2C#0
U$62: #D2_#0
U$63: #0#5A#0
U$64: #0#1A#0
U$66: MEAS81
U$67: CHG0
U$68: STAT0
U$69: #JP1#0
U$70: RST0
U$71: #_A5#TX#0
U$72: A80
U$73: #SDA#B4_#0
U$74: #SCL#B3_#0
U$75: ORDERING_INSTRUCTIONS
U$76: FOUR_LAYER_WARNING
U$77: #D3_#0
U$78: DBG0
U$79: #_C7#FREE#0
U$80: A0
U$81: B0
U$82: #D3#4
U$83: #CHG_I#0
U$84: SILICON_LABS_LOGO_9MM
